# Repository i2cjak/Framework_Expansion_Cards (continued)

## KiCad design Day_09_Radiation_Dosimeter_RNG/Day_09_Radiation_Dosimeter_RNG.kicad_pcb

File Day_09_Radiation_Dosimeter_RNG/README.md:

# Day 09 — Solid-State PIN Radiation Dosimeter & Quantum Decay Hardware RNG

A pocket solid-state ionizing-radiation dosimeter, pulse-height spectrometer, and `/dev/hwrng` true quantum hardware random-number generator built into a `26.0 × 30.0 mm` Framework Laptop Expansion Card.

## Hardware Architecture

1. **Dual Parallel Depleted Silicon PIN Detector (`D3`, `D4` — `2×` OSRAM `BPW34S-Z`, `15.0 mm²` Active Area):**
   - Two `7.5 mm²` intrinsic-layer silicon PIN diodes wired in parallel inside an exposed-ENIG **Faraday & optical shield-can frame** (`10.5 × 10.3 mm` solderable perimeter ring with 12 Faraday stitching vias to the unbroken `In1.Cu` ground plane).
   - Soldering a tinned-steel EMI shield lid (or copper foil tape) over the gold ring blocks visible/IR photons completely while letting X-ray, gamma, and energetic beta particles ionize electron-hole pairs inside the depleted silicon bulk.

2. **`+13.3 V` 4-Stage Dickson Depletion Multiplier & `> 140 dB` Ripple Filter (`D5`, `D6` — `2× BAV99`):**
   - Driven out-of-phase by `TIM1` `100 kHz` push-pull clocks (`PA8` / `PA9`) from `+5.0 V` `VBUS` across three `50 V` flying capacitors (`C11`–`C13`), elevating cathode reverse bias to `+13.3 V` so each `BPW34S-Z` depletes from `72 pF` (`0 V`) down to `~12 pF`.
   - Two cascaded low-pass RC poles (`100 kΩ + 100 nF`, `f_c = 15.9 Hz` followed by `1 MΩ + 100 nF`, `f_c = 1.59 Hz`) attenuate `100 kHz` charge-pump switching ripple below Johnson thermal noise before reaching the PIN cathodes, while an `11:1` divider (`R12`/`R13`) provides closed-loop `HV_RAW` telemetry on `PA0` (`ADC_IN0`).

3. **Femtoamp CMOS Charge-Sensitive Pre-Amplifier & CR-RC Pulse Shaper (`U4`, `U5` — `2×` TI `TLV9061IDBVR`):**
   - Physically separated single-channel `SOT-23-5` CMOS op-amps (`0.5 pA` input bias, `10 MHz` GBW, `10 nV/√Hz` input voltage noise) eliminate dual-op-amp leadframe crosstalk between the high-gain shaper output and the `2.2 pF` charge-integration node.
   - **Stage 1 (`U4` CSA):** `C18 = 2.2 pF C0G` feedback capacitor (`0.45 mV/fC` charge gain) in parallel with `R14 = 10 MΩ` (`τ = 22 µs`) biased at `+0.58 V` (`VBIAS_0V58`) on dedicated RC-isolated analog power (`V33_ANA`).
   - **Stage 2 (`U5` CR-RC Shaper):** `C19 = 100 pF C0G` + `R15 = 2.2 kΩ` differentiator feeding a `-45.5×` active integrator (`R16 = 100 kΩ || C20 = 22 pF C0G`, `τ = 2.2 µs`), converting negative CSA steps into clean positive unipolar pulses (`+0.58 V` baseline to `+3.30 V` full-scale).

4. **Hardware Discriminator, Spectroscopy & Unbiased Quantum Entropy (`U3` — `STM32F072CBT6`):**
   - Crystal-less Full-Speed USB (`HSI48` + `CRS` `1 kHz` USB `SOF` trim) streams conditioned entropy to Linux `/dev/hwrng` and pulse-height histograms over USB CDC.
   - On-chip `DAC1` (`PA4`) sets a software-programmable millivolt threshold on `COMP1_INM`; `PULSE_OUT` on `PA1` triggers `COMP1` (`50 ns`) to timestamp `48 MHz` `TIM2` arrival intervals (`t2 - t1` vs `t4 - t3` unbiased Poisson interval comparison + Von Neumann whitening) and triggers `1 Msps` `ADC_IN1` peak capture for gamma energy spectroscopy.

## Fabrication & Build

All components are sourced from the fab's stock on a `0.8 mm` 4-layer purple-soldermask ENIG stackup (`Day_09_Radiation_Dosimeter_RNG.fab.json`). Regenerate ERC/DRC reports, Gerbers, placement files, STEP model, and 3D renders with:

```bash
python3 build.py
```

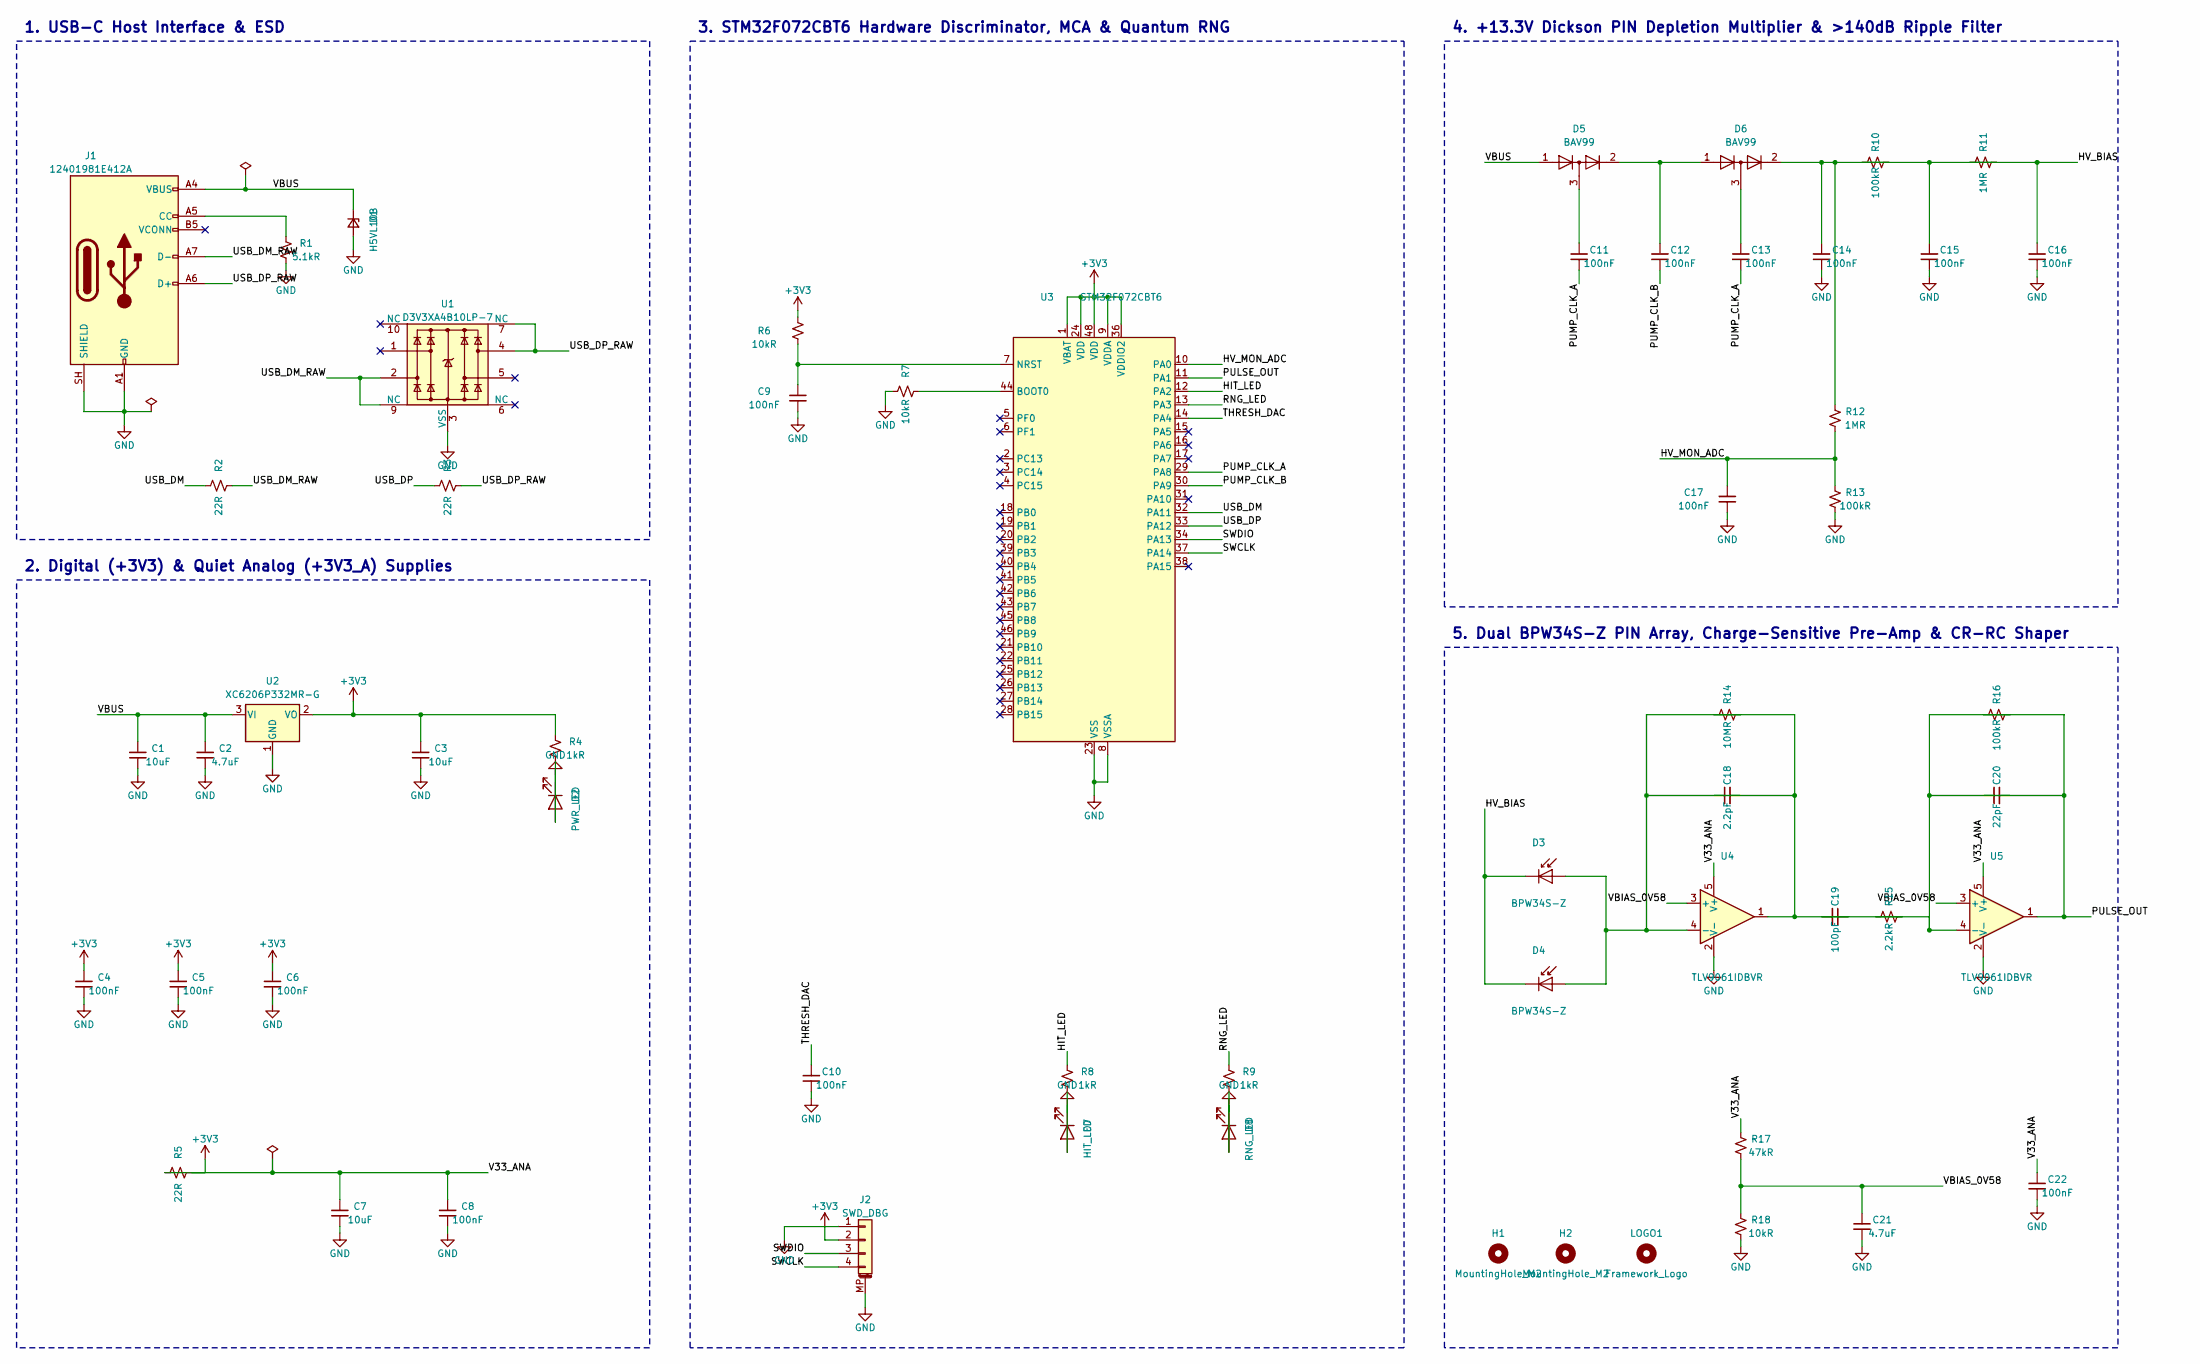
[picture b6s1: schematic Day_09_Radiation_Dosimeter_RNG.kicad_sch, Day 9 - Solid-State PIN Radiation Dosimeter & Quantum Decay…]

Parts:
C1, C3, C7: 10uF; C_0805_2012Metric; MPN CL21A106KAYNNNE; LCSC C15850
C2, C21: 4.7uF; C_0603_1608Metric; MPN CL10A475KO8NNNC; LCSC C19666
C4, C5, C6, C8, C9, C10, C17, C22: 100nF; C_0402_1005Metric; MPN CL05B104KB54PNC; LCSC C307331
C11, C12, C13, C14, C15, C16: 100nF; C_0603_1608Metric; MPN CC0603KRX7R9BB104; LCSC C14663
C18: 2.2pF; C_0603_1608Metric; MPN 0603CG2R2C500NT; LCSC C1651
C19: 100pF; C_0603_1608Metric; MPN CL10C101JB8NNNC; LCSC C14858
C20: 22pF; C_0603_1608Metric; MPN CL10C220JB8NNNC; LCSC C1653
D1: H5VL10B; D_SOD-882; MPN H5VL10B; LCSC C7420372
D2: PWR_LED; LED_0603_1608Metric; MPN KT-0603G; LCSC C2297
D3, D4: BPW34S-Z; Osram_BPW34S-SMD; MPN BPW34S-Z; LCSC C67891
D5, D6: BAV99; SOT-23; MPN BAV99; LCSC C7420336
D7: HIT_LED; LED_0603_1608Metric; MPN KT-0603R; LCSC C2286
D8: RNG_LED; LED_0603_1608Metric; MPN KT-0603W; LCSC C2290
H1, H2: MountingHole_M2; MountingHole_2.2mm_M2
J1: 12401981E412A; USB_C_Plug_Amphenol_12401981E412A; MPN 12401981E412A; LCSC C5428559
J2: SWD_DBG; JST_SH_SM04B-SRSS-TB_1x04-1MP_P1.00mm_Horizontal; MPN SM04B-SRSS-TB(LF)(SN); LCSC C160404
LOGO1: Framework_Logo; Framework-Logo_1.5mm_SilkScreen
R1: 5.1kR; R_0402_1005Metric; MPN 0402WGF5101TCE; LCSC C25905
R2, R3, R5: 22R; R_0402_1005Metric; MPN 0402WGF220JTCE; LCSC C25092
R4, R8, R9: 1kR; R_0402_1005Metric; MPN 0402WGF1001TCE; LCSC C11702
R6, R7, R18: 10kR; R_0402_1005Metric; MPN 0402WGF1002TCE; LCSC C25744
R10, R13, R16: 100kR; R_0402_1005Metric; MPN 0402WGF1003TCE; LCSC C25741
R11, R12: 1MR; R_0603_1608Metric; MPN 0603WAF1004T5E; LCSC C22935
R14: 10MR; R_0603_1608Metric; MPN 0603WAF1005T5E; LCSC C7250
R15: 2.2kR; R_0402_1005Metric; MPN 0402WGF2201TCE; LCSC C25879
R17: 47kR; R_0402_1005Metric; MPN 0402WGF4702TCE; LCSC C25792
U1: D3V3XA4B10LP-7; Diodes_UDFN-10_1x2.5mm_P0.5mm; MPN D3V3XA4B10LP-7; LCSC C1980462
U2: XC6206P332MR-G; SOT-23; MPN XC6206P332MR-G; LCSC C5446
U3: STM32F072CBT6; LQFP-48_7x7mm_P0.5mm; MPN STM32F072CBT6; LCSC C81720
U4, U5: TLV9061IDBVR; SOT-23-5; MPN TLV9061IDBVR; LCSC C398358

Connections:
/HIT_LED: R8.1, U3.12 (PA2)
/HV_BIAS: C16.1, D3.1 (K), D4.1 (K), R11.1
/HV_MON_ADC: C17.1, R12.2, R13.1, U3.10 (PA0)
/PULSE_OUT: C20.1, R16.1, U3.11 (PA1), U5.1
/PUMP_CLK_A: C11.2, C13.2, U3.29 (PA8)
/PUMP_CLK_B: C12.2, U3.30 (PA9)
/RNG_LED: R9.1, U3.13 (PA3)
/SWCLK: J2.4, U3.37 (PA14)
/SWDIO: J2.3, U3.34 (PA13)
/THRESH_DAC: C10.1, U3.14 (PA4)
/USB_DM: R2.1, U3.32 (PA11)
/USB_DM_RAW: J1.A7 (D-), R2.2, U1.2, U1.9 (NC)
/USB_DP: R3.1, U3.33 (PA12)
/USB_DP_RAW: J1.A6 (D+), R3.2, U1.4, U1.7 (NC)
/V33_ANA: C7.1, C8.1, C22.1, R5.1, R17.1, U4.5 (V+), U5.5 (V+)
/VBIAS_0V58: C21.1, R17.2, R18.1, U4.3 (+), U5.3 (+)
/VBUS: C1.1, C2.1, D1.1 (K), D5.1 (K), J1.A4 (VBUS), J1.A9 (VBUS), J1.B4 (VBUS), J1.B9 (VBUS), U2.3 (VI)
unnamed: C11.1, D5.3 (K)
unnamed: C13.1, D6.3 (K)
unnamed: C15.1, R10.1, R11.2
unnamed: C18.1, C19.2, R14.1, U4.1
unnamed: C19.1, R15.2
unnamed: C18.2, D3.2 (A), D4.2 (A), R14.2, U4.4 (-)
unnamed: C12.1, D5.2 (A), D6.1 (K)
unnamed: C14.1, D6.2 (A), R10.2, R12.1
unnamed: J1.A5 (CC), R1.1
unnamed: R7.2, U3.44 (BOOT0)
unnamed: C9.1, R6.2, U3.7 (NRST)
unnamed: C20.2, R15.1, R16.2, U5.4 (-)

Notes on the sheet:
1. USB-C Host Interface & ESD
2. Digital (+3V3) & Quiet Analog (+3V3_A) Supplies
3. STM32F072CBT6 Hardware Discriminator, MCA & Quantum RNG
4. +13.3V Dickson PIN Depletion Multiplier & >140dB Ripple Filter
5. Dual BPW34S-Z PIN Array, Charge-Sensitive Pre-Amp & CR-RC Shaper

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
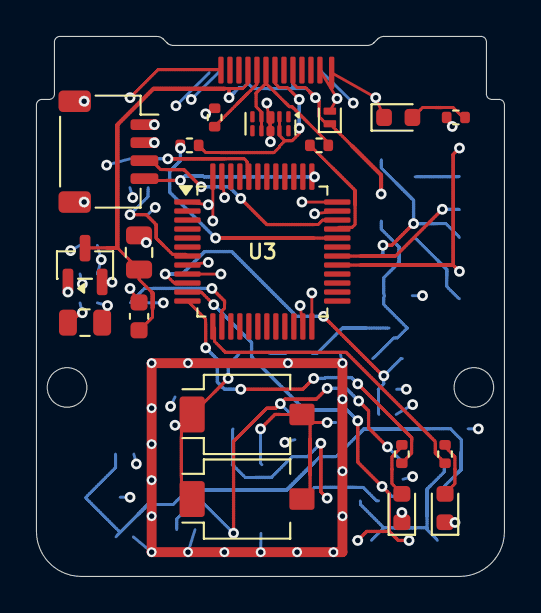
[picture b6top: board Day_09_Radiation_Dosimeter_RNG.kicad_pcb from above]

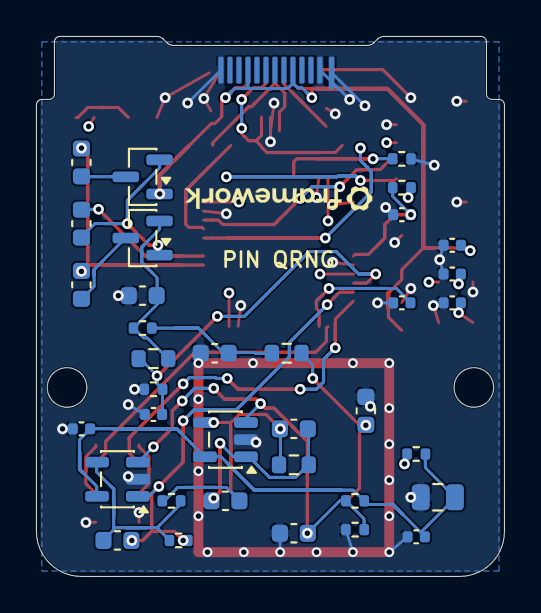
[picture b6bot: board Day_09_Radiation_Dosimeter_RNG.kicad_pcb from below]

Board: 4 copper layers, 26.0 x 30.0 mm, 58 parts (36 on the bottom side), 34 nets.

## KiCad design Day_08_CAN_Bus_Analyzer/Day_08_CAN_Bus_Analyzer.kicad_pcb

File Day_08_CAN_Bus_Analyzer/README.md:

# Day 08 — `1 Mbps` ISO-11898 CAN 2.0B Bus Analyzer (`gs_usb` SocketCAN)

A flush-fitting Framework Laptop Expansion Card implementing a native Linux mainline **`gs_usb` / candleLight SocketCAN** `1 Mbps` ISO-11898-2 CAN 2.0B analyzer with **galvanically isolated solid-state `120 Ω` termination switching**, hardware listen-only mode, `±24 V` automotive surge clamping, and `0–36.3 V` CAN-harness supply rail telemetry on a locking DroneCAN/Cyphal `4`-pin JST-GH bezel port.

---

## Hardware Architecture & Engineering Decisions

### 1. Simultaneous Full-Speed USB + `1 Mbps` `bxCAN` (`STM32F072CBT6` + `±10 ppm` Quartz)
- Unlike `STM32F103x8` devices (which share a single 512 B SRAM block and IRQ vector between USB and `CAN1`), **`U3` (`STM32F072CBT6`)** provides a dedicated `1 KB` USB packet buffer at `0x40006000` (`PA11`/`PA12`) alongside an independent `bxCAN` controller (`PB8`/`PB9`), sustaining **100% `1 Mbps` CAN bus load** over USB without dropped frames.
- **`Y1` (`X32258MOB4SI` `8.000 MHz` `±10 ppm` `3225` quartz crystal)** clocks the `bxCAN` bit-timing engine (`48.000 MHz` via `×6` PLL: `BRP = 3`, `16 TQ`, `TS1 = 13`, `TS2 = 2`, `87.5%` CiA sample point), exceeding ISO-11898-1 oscillator accuracy (`±0.15%`) by **`150×`** while `HSI48` + `CRS` clocks USB Full-Speed.

### 2. Opto-Isolated `120 Ω` PhotoMOS Solid-State Termination (`TLP172AM`)
- Switching a `120 Ω` resistor across a differential CAN bus with a bare GPIO-driven N-MOSFET fails under common-mode excursions (`-2 V` to `+7 V` operational, `±24 V` fault) due to `V_GS` modulation and body-diode conduction.
- **`U5` (Toshiba `TLP172AM` `SOP-4` PhotoMOS solid-state relay, `60 V` blocking, `1.0 Ω` `R_on`, `3.75 kVrms` isolation)** places back-to-back optically driven MOSFETs in series with **`R14` (`120 Ω` `1%` `0805` `125 mW`)**:
  - **Enabled (`PB1 = HIGH`):** `R_term = 120.0 + 1.0 = 121.0 Ω` (within `< 1%` of nominal `120 Ω`, ISO-11898 window `118–130 Ω`), illuminating the bezel `TERM` indicator (`D5`).
  - **Disabled (`PB1 = LOW`):** Bidirectional `±60 V` open circuit with `< 15 pF` symmetric off-capacitance and zero ground-loop or common-mode coupling—toggleable directly via `ip link set can0 type can termination 120`.

### 3. Transceiver, `±24 V` Automotive Protection & `0–36 V` DroneCAN Bus Sense
- **`U4` (`SN65HVD230DR`):** `3.3 V` `1 Mbps` ISO-11898 transceiver with `R9` (`10 kΩ` recessive pull-up on `D` during MCU reset) and `PB0`-controlled `Rs` pin supporting hardware **Listen-Only / Silent** mode (`ip link set can0 type can listen-only on`).
- **`D6` (`PESD2CAN` `SOT-23`) + `C13`/`C14` (`22 pF` `50 V` `C0G`):** Dual bidirectional `24 V` CAN surge clamp (`IEC 61000-4-2 ±30 kV`) placed immediately behind **`J2` (`SM04B-GHS-TB` locking 4-pin `1.25 mm` JST-GH)** wired to the standard **DroneCAN / Cyphal / Pixhawk / VESC** pinout (`1: V_CAN`, `2: CAN_H`, `3: CAN_L`, `4: GND`).
- **`V_CAN` Voltage Sense (`PA0 / ADC_IN0`):** `100 kΩ / 10 kΩ` `1%` divider (`11:1`, `0–36.3 V` full-scale) filtered by `100 nF` (`C15`) and clamped by `D7` (`H5VL10B` TVS), strictly isolated from host `VBUS` so external `12 V / 24 V` vehicle or drone batteries can never back-feed the laptop.

---

## Building PCB & Firmware

```bash
# Regenerate ERC/DRC reports, Gerbers, BOM/CPL (from the fab's stock), and 3D renders
cd Day_08_CAN_Bus_Analyzer && python3 build.py

# Compile STM32F072CBT6 gs_usb / bxCAN firmware
make -C firmware
```

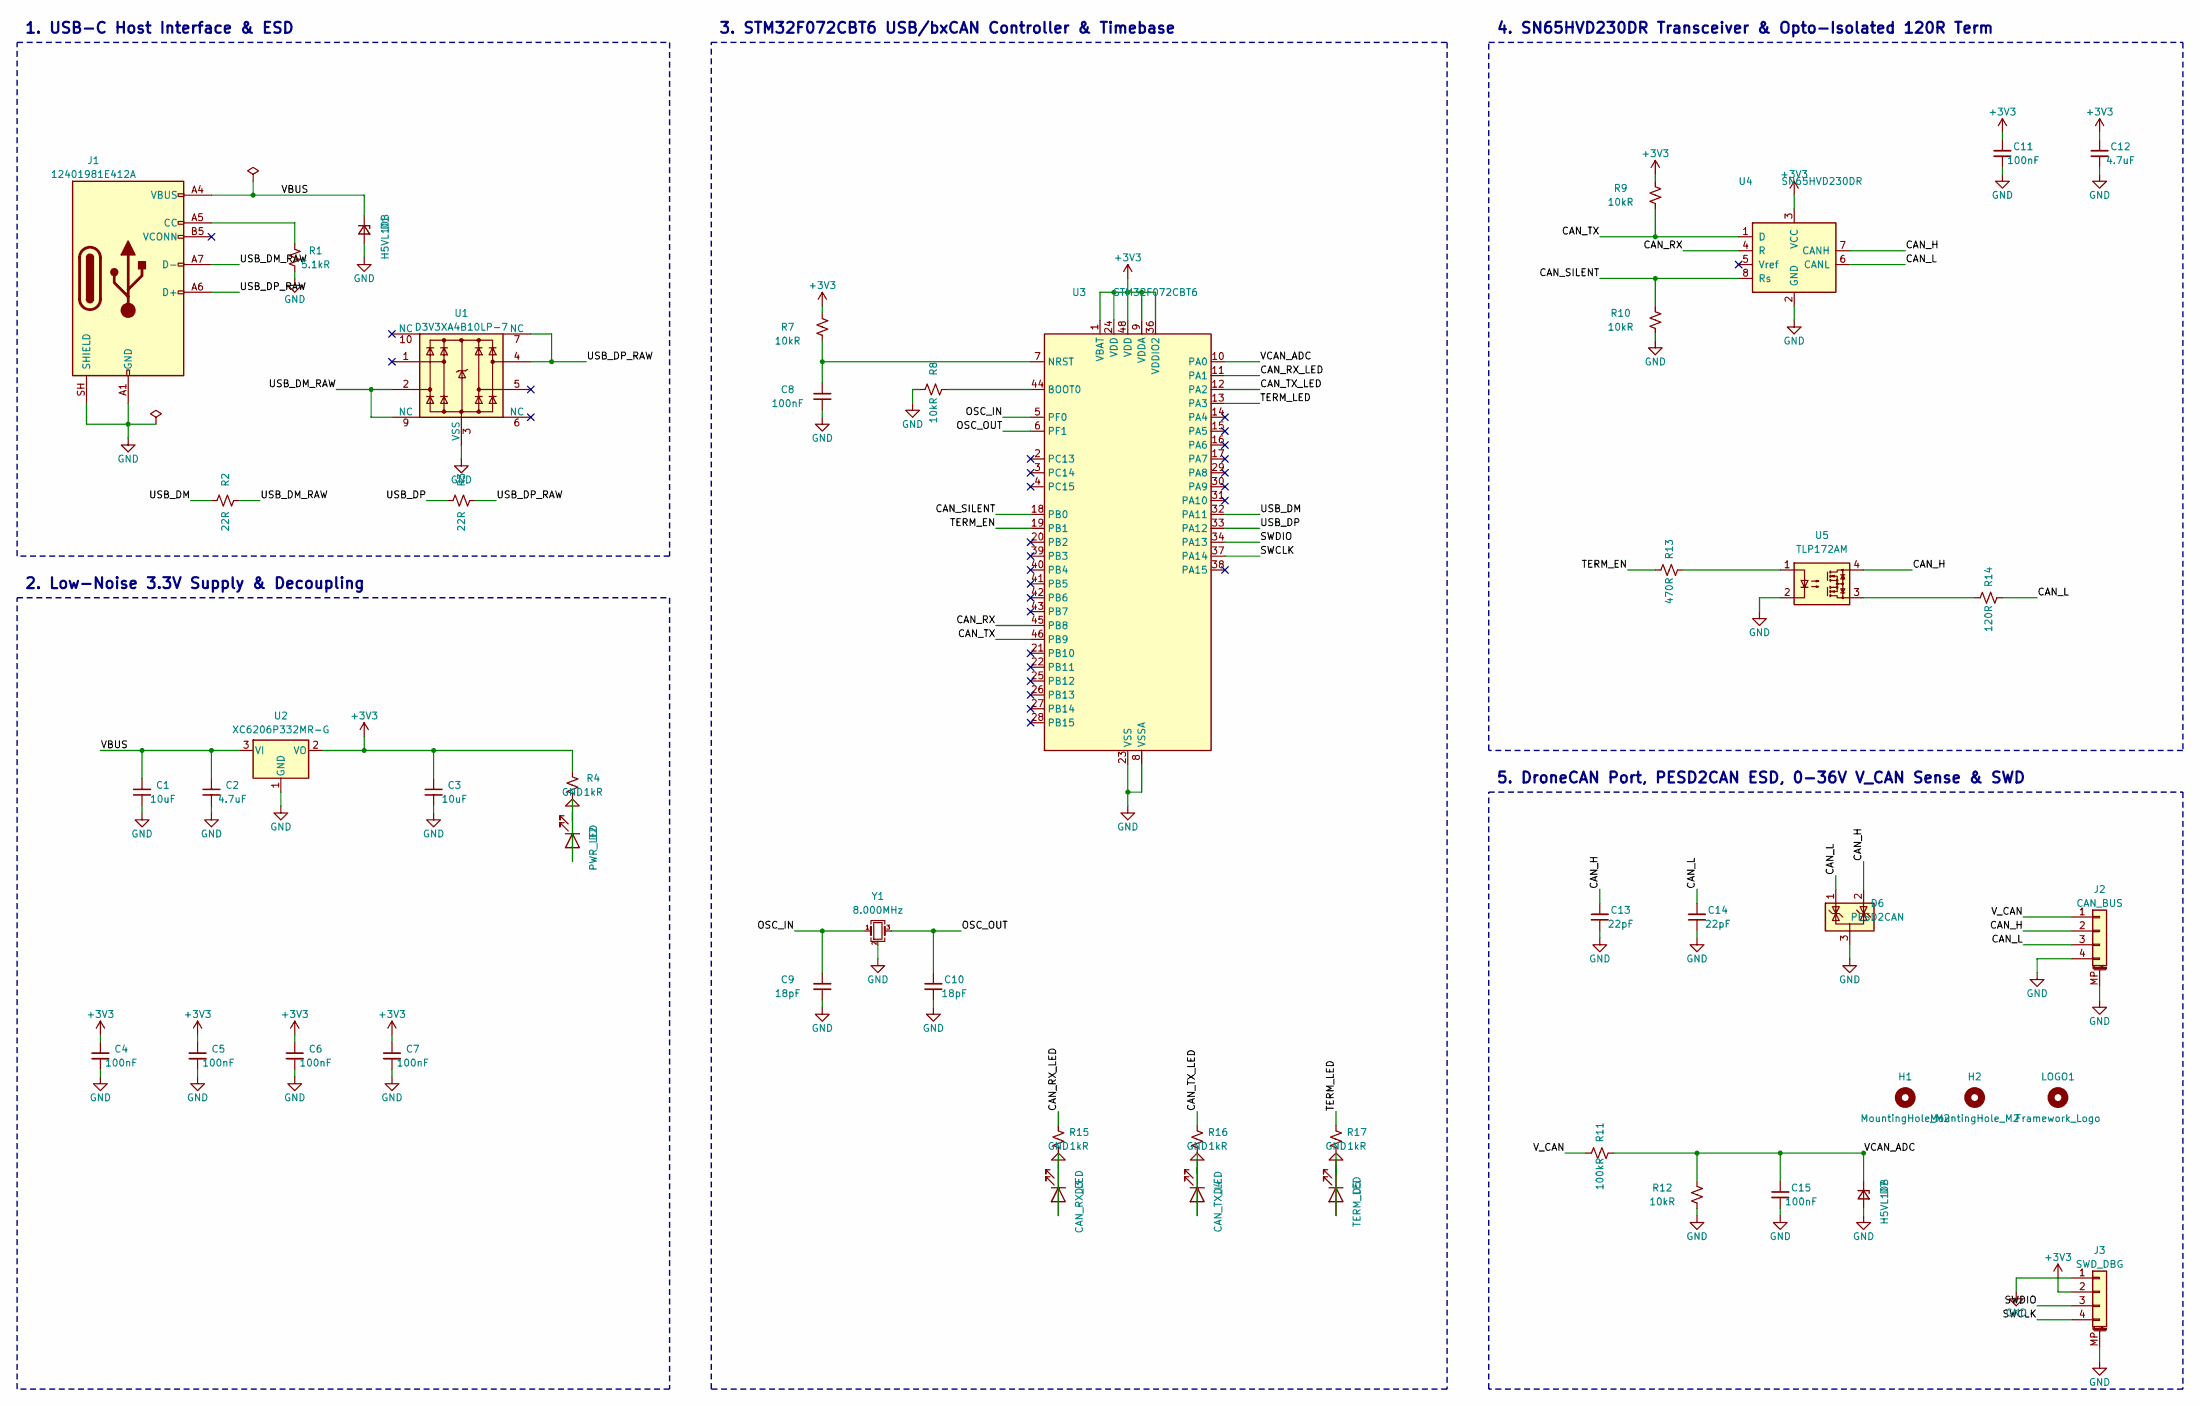
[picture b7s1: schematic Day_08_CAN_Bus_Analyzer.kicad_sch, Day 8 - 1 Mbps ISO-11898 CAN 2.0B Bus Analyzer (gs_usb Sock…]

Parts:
C1, C3: 10uF; C_0805_2012Metric; MPN CL21A106KAYNNNE; LCSC C15850
C2, C12: 4.7uF; C_0603_1608Metric; MPN CL10A475KO8NNNC; LCSC C19666
C4, C5, C6, C7, C8, C11, C15: 100nF; C_0402_1005Metric; MPN CL05B104KB54PNC; LCSC C307331
C9, C10: 18pF; C_0402_1005Metric; MPN 0402CG180J500NT; LCSC C1549
C13, C14: 22pF; C_0402_1005Metric; MPN 0402CG220J500NT; LCSC C1555
D1, D7: H5VL10B; D_SOD-882; MPN H5VL10B; LCSC C7420372
D2: PWR_LED; LED_0603_1608Metric; MPN KT-0603W; LCSC C2290
D3: CAN_RX_LED; LED_0603_1608Metric; MPN KT-0603W; LCSC C2290
D4: CAN_TX_LED; LED_0603_1608Metric; MPN KT-0603R; LCSC C2286
D5: TERM_LED; LED_0603_1608Metric; MPN KT-0603R; LCSC C2286
D6: PESD2CAN; SOT-23; MPN PESD2CAN; LCSC C2687131
H1, H2: MountingHole_M2; MountingHole_2.2mm_M2
J1: 12401981E412A; USB_C_Plug_Amphenol_12401981E412A; MPN 12401981E412A; LCSC C5428559
J2: CAN_BUS; JST_GH_SM04B-GHS-TB_1x04-1MP_P1.25mm_Horizontal; MPN SM04B-GHS-TB(LF)(SN); LCSC C189895
J3: SWD_DBG; JST_SH_SM04B-SRSS-TB_1x04-1MP_P1.00mm_Horizontal; MPN SM04B-SRSS-TB(LF)(SN); LCSC C160404
LOGO1: Framework_Logo; Framework-Logo_1.5mm_SilkScreen
R1: 5.1kR; R_0402_1005Metric; MPN 0402WGF5101TCE; LCSC C25905
R2, R3: 22R; R_0402_1005Metric; MPN 0402WGF220JTCE; LCSC C25092
R4, R15, R16, R17: 1kR; R_0402_1005Metric; MPN 0402WGF1001TCE; LCSC C11702
R7, R8, R9, R10, R12: 10kR; R_0402_1005Metric; MPN 0402WGF1002TCE; LCSC C25744
R11: 100kR; R_0402_1005Metric; MPN 0402WGF1003TCE; LCSC C25741
R13: 470R; R_0402_1005Metric; MPN 0402WGF4700TCE; LCSC C25117
R14: 120R; R_0805_2012Metric; MPN 0805W8F1200T5E; LCSC C17437
U1: D3V3XA4B10LP-7; Diodes_UDFN-10_1x2.5mm_P0.5mm; MPN D3V3XA4B10LP-7; LCSC C1980462
U2: XC6206P332MR-G; SOT-23; MPN XC6206P332MR-G; LCSC C5446
U3: STM32F072CBT6; LQFP-48_7x7mm_P0.5mm; MPN STM32F072CBT6; LCSC C81720
U4: SN65HVD230DR; SOIC-8_3.9x4.9mm_P1.27mm; MPN SN65HVD230DR; LCSC C12084
U5: TLP172AM; SOP-4_3.8x4.1mm_P2.54mm; MPN TLP172AM(TPL,E; LCSC C2152276
Y1: 8.000MHz; Crystal_SMD_3225-4Pin_3.2x2.5mm; MPN X32258MOB4SI; LCSC C2682775

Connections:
/CAN_H: C13.1, D6.2 (K), J2.2, U4.7 (CANH), U5.4
/CAN_L: C14.1, D6.1 (K), J2.3, R14.2, U4.6 (CANL)
/CAN_RX: U3.45 (PB8), U4.4 (R)
/CAN_RX_LED: R15.1, U3.11 (PA1)
/CAN_SILENT: R10.1, U3.18 (PB0), U4.8 (Rs)
/CAN_TX: R9.2, U3.46 (PB9), U4.1 (D)
/CAN_TX_LED: R16.1, U3.12 (PA2)
/OSC_IN: C9.1, U3.5 (PF0), Y1.1
/OSC_OUT: C10.1, U3.6 (PF1), Y1.3
/SWCLK: J3.4, U3.37 (PA14)
/SWDIO: J3.3, U3.34 (PA13)
/TERM_EN: R13.1, U3.19 (PB1)
/TERM_LED: R17.1, U3.13 (PA3)
/USB_DM: R2.1, U3.32 (PA11)
/USB_DM_RAW: J1.A7 (D-), R2.2, U1.2, U1.9 (NC)
/USB_DP: R3.1, U3.33 (PA12)
/USB_DP_RAW: J1.A6 (D+), R3.2, U1.4, U1.7 (NC)
/VBUS: C1.1, C2.1, D1.1 (K), J1.A4 (VBUS), J1.A9 (VBUS), J1.B4 (VBUS), J1.B9 (VBUS), U2.3 (VI)
/VCAN_ADC: C15.1, D7.1 (K), R11.2, R12.1, U3.10 (PA0)
/V_CAN: J2.1, R11.1
unnamed: J1.A5 (CC), R1.1
unnamed: R13.2, U5.1
unnamed: R14.1, U5.3
unnamed: R8.2, U3.44 (BOOT0)
unnamed: C8.1, R7.2, U3.7 (NRST)

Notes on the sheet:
1. USB-C Host Interface & ESD
2. Low-Noise 3.3V Supply & Decoupling
3. STM32F072CBT6 USB/bxCAN Controller & Timebase
4. SN65HVD230DR Transceiver & Opto-Isolated 120R Term
5. DroneCAN Port, PESD2CAN ESD, 0-36V V_CAN Sense & SWD

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
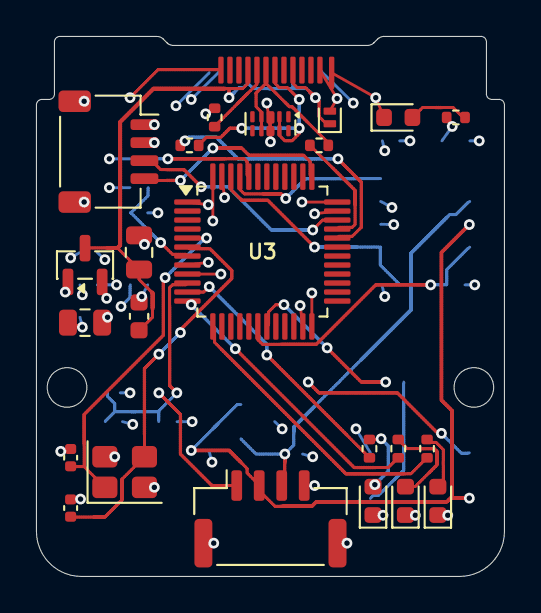
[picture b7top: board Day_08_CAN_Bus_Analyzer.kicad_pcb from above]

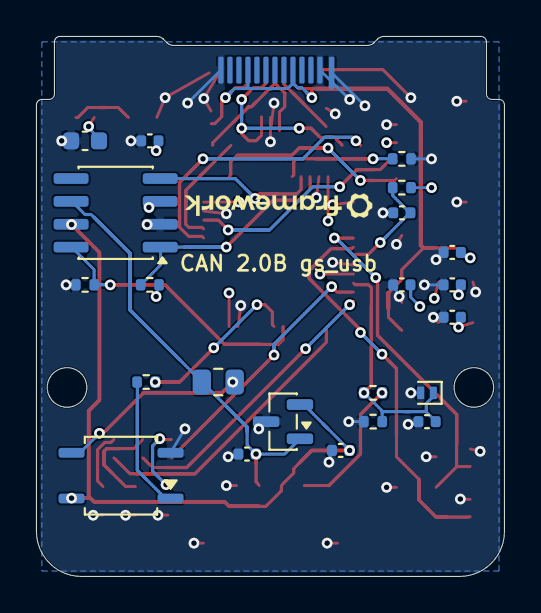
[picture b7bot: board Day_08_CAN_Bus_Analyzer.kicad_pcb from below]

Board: 4 copper layers, 26.0 x 30.0 mm, 49 parts (23 on the bottom side), 31 nets.

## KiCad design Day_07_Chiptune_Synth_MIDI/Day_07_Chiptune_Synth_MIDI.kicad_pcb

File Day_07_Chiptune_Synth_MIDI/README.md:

# Day 07 — Polyphonic FM / Chiptune Hardware Synthesizer & Type-A MIDI Expansion Card

A pocket hardware music workstation inside a `26.0 × 30.0 mm` Framework Expansion Card bay (`IDEAS.md` Concept #10). Enumerates over USB-C as a class-compliant **USB-MIDI 1.0** instrument using crystal-less `HSI48` USB-SOF clock recovery (`CRS`), synthesizes **4-voice polyphonic 2-operator FM + pulse/duty + wavetable/triangle + LFSR noise chiptune audio** in real time on an `STM32F072CBT6`, streams `48 kHz` stereo digital audio over hardware `I2S2` into a **Texas Instruments `PCM5102APWR` 32-bit / 384 kHz DirectPath™ charge-pump DAC** (`112 dB` SNR, ground-centered `2.1 Vrms` stereo output with zero DC-blocking output capacitors), and provides both a **gold-plated `3.5 mm` stereo headphone/line-out jack (`J2`)** and a **locking `1.25 mm` 3-pin MMA Type-A hardware MIDI Out port (`J3`)** plus a **4-channel front-bezel voice activity LED bar (`D3..D6`)**.

---

## Architecture & Key Specifications

| Subsystem | Implementation | Key Rating / Performance |
| :--- | :--- | :--- |
| **USB-MIDI & Synth Engine (`U3`)** | `STM32F072CBT6` (`48 MHz` Cortex-M0, `128 KB` Flash, `16 KB` SRAM) | Crystal-less `HSI48` trimmed to `±0.05%` via `1 kHz` USB `SOF` (`CRS`); hardware `I2S2` master + `USART1` `31.25 kbaud` MIDI |
| **Stereo Audio DAC (`U4`)** | `PCM5102APWR` (`TSSOP-20`, internal negative charge pump + internal PLL) | `32-bit / 384 kHz` max (`48 kHz` native synth engine), `112 dB` dynamic range, `-93 dB` THD+N, `2.1 Vrms` ground-centered DirectPath™ output (`SCK=GND` 3-wire BCK-PLL mode) |
| **Stereo Output (`J2`)** | `PJ-320D-4A` gold-plated `3.5 mm` SMD TRS/TRRS jack + `22 Ω` series isolation (`R5`, `R6`) | Drives studio line inputs and `32 Ω+` headphones directly down to `0 Hz` without bass roll-off |
| **Hardware MIDI Out (`J3`)** | Locking `1.25 mm` 3-pin JST-GH (`SM03B-GHS-TB`) wired per **MMA 3.3 V Type-A TRS MIDI** | Pin 1 (`Tip/Sink`) via `22 Ω` (`R9`) from `PA9/USART1_TX`, Pin 2 (`Ring/Source`) via `22 Ω` (`R10`) from `+3V3`, Pin 3 (`Sleeve`) = `GND` |
| **Front-Bezel Voice Bar (`D3..D6`)** | 4× `0603` SMD LEDs (`PA0..PA3`, alternating Red/White) | Per-voice gate & envelope trigger indicators (Voices 1–2 FM/Pulse, Voice 3 Triangle/Wave, Voice 4 LFSR Noise/Drums) |
| **USB Protection & Power** | `H5VL10B` TVS (`D1`), `D3V3XA4B10LP-7` low-cap ESD (`U1`), `XC6206P332MR-G` `3.3 V` LDO (`U2`) | `5.1 kΩ` `CC1` sink (`R1`), `< 45 mA` total card draw from `5 V` `VBUS` |
| **4-Layer Stackup** | `0.8 mm` 4-Layer Red ENIG (`F.Cu` / `In1.Cu GND` / `In2.Cu +3V3` / `B.Cu GND`) | Unbroken `In1.Cu` ground reference plane isolating digital USB/MCU return currents from analog `OUTL`/`OUTR` |

---

## Pin Map (`STM32F072CBT6`)

| MCU Pin | Signal | Target / Function |
| :--- | :--- | :--- |
| `PA11` / `PA12` | `USB_DM` / `USB_DP` | USB 2.0 Full-Speed Device (`USB-MIDI 1.0` + `CRS` `1 kHz` SOF trim, via `22 Ω` `R2`/`R3` + `U1` ESD) |
| `PB12` (`I2S2_WS`) | `I2S_LRCK` | `PCM5102A` Pin 15 (`LRCK`, `48 kHz` stereo frame clock) |
| `PB13` (`I2S2_CK`) | `I2S_BCK` | `PCM5102A` Pin 13 (`BCK`, `1.536 MHz` bit clock; drives `PCM5102A` internal PLL with `SCK=GND`) |
| `PB15` (`I2S2_SD`) | `I2S_DIN` | `PCM5102A` Pin 14 (`DIN`, 16-bit/32-bit stereo I2S PCM stream) |
| `PB14` | `DAC_XSMT` | `PCM5102A` Pin 17 (`XSMT` soft-mute control; `10 kΩ` pull-down `R15` keeps DAC pop-free during reset) |
| `PA9` (`USART1_TX`) | `MIDI_TX` | `31,250 baud` 8N1 Hardware MIDI Out (`R9 = 22 Ω` sink, `R10 = 22 Ω` `+3V3` source on `J3`) |
| `PA0 .. PA3` | `VOICE_LED1..4` | Front-bezel 4-channel polyphonic voice gate LEDs (`D3..D6`) |
| `PA13` / `PA14` | `SWDIO` / `SWCLK` | `J4` 4-pin `1.0 mm` JST-SH SWD debug & flash header |

---

## Building & Verifying

### Hardware (KiCad 10 ERC, DRC, Gerbers, BOM, 3D STEP & Renders)
```bash
cd Day_07_Chiptune_Synth_MIDI
python3 build.py
```
- **ERC:** `0` errors, `0` warnings
- **DRC:** `0` violations, `0` unconnected items, `0` schematic parity issues
- **Fabrication Spec:** [`Day_07_Chiptune_Synth_MIDI.fab.json`](./Day_07_Chiptune_Synth_MIDI.fab.json) (`4` layers, `0.8 mm` thickness, Red solder mask, ENIG finish, all SMD components verified in stock at the fab)

### Firmware (`arm-none-eabi-gcc`)
```bash
cd Day_07_Chiptune_Synth_MIDI/firmware
make
```
Builds `build/chiptune_synth_midi.elf` and `.bin` with `0` warnings — configuring `HSI48` + `CRS` USB-SOF auto-trimming, `SPI2`/`I2S2` `48 kHz` master audio streaming to `PCM5102APWR` (`PB14` pop-free unmute sequencing), `31,250 baud` `USART1` hardware MIDI Out mirroring, 4-voice DDS phase-accumulated FM / pulse / triangle / 15-bit LFSR percussion synthesis, and `PA0..PA3` voice activity LEDs.

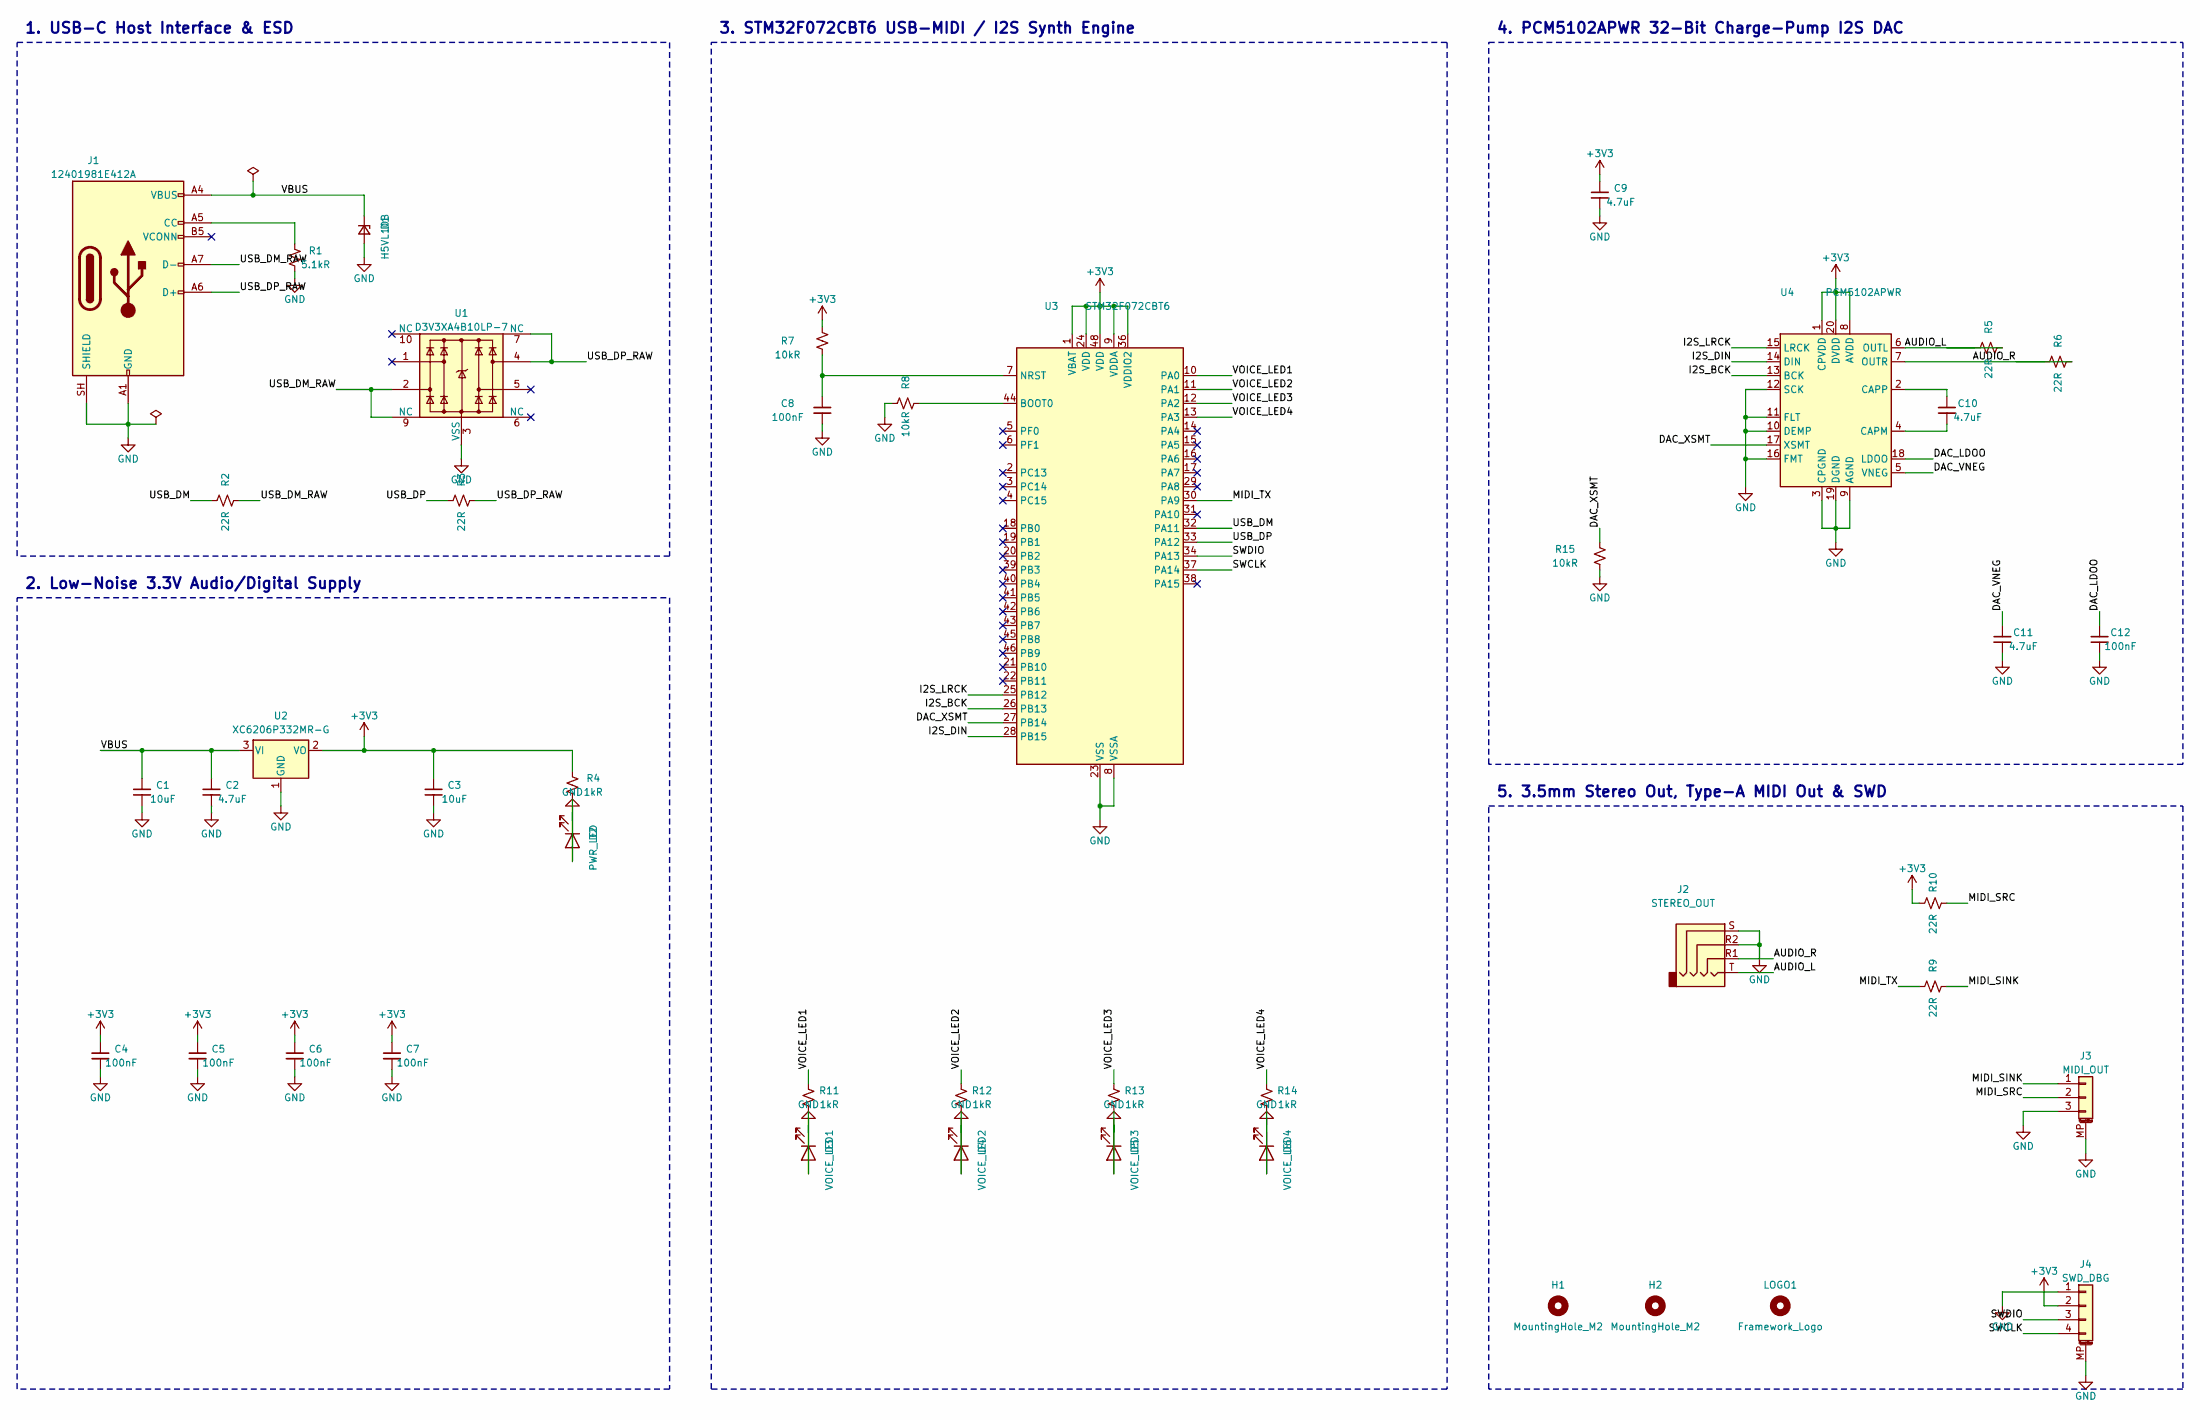
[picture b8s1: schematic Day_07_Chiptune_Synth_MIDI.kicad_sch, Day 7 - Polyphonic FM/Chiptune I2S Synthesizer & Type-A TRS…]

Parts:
C1, C3: 10uF; C_0805_2012Metric; MPN CL21A106KAYNNNE; LCSC C15850
C2, C9, C10, C11: 4.7uF; C_0603_1608Metric; MPN CL10A475KO8NNNC; LCSC C19666
C4, C5, C6, C7, C8, C12: 100nF; C_0402_1005Metric; MPN CL05B104KB54PNC; LCSC C307331
D1: H5VL10B; D_SOD-882; MPN H5VL10B; LCSC C7420372
D2: PWR_LED; LED_0603_1608Metric; MPN KT-0603W; LCSC C2290
D3: VOICE_LED1; LED_0603_1608Metric; MPN KT-0603R; LCSC C2286
D4: VOICE_LED2; LED_0603_1608Metric; MPN KT-0603W; LCSC C2290
D5: VOICE_LED3; LED_0603_1608Metric; MPN KT-0603R; LCSC C2286
D6: VOICE_LED4; LED_0603_1608Metric; MPN KT-0603W; LCSC C2290
H1, H2: MountingHole_M2; MountingHole_2.2mm_M2
J1: 12401981E412A; USB_C_Plug_Amphenol_12401981E412A; MPN 12401981E412A; LCSC C5428559
J2: STEREO_OUT; PJ-320D-4A_Bezel; MPN PJ-320D-4A; LCSC C95562
J3: MIDI_OUT; JST_GH_SM03B-GHS-TB_1x03-1MP_P1.25mm_Horizontal; MPN SM03B-GHS-TB(LF)(SN); LCSC C514175
J4: SWD_DBG; JST_SH_SM04B-SRSS-TB_1x04-1MP_P1.00mm_Horizontal; MPN SM04B-SRSS-TB(LF)(SN); LCSC C160404
LOGO1: Framework_Logo; Framework-Logo_1.5mm_SilkScreen
R1: 5.1kR; R_0402_1005Metric; MPN 0402WGF5101TCE; LCSC C25905
R2, R3, R5, R6, R9, R10: 22R; R_0402_1005Metric; MPN 0402WGF220JTCE; LCSC C25092
R4, R11, R12, R13, R14: 1kR; R_0402_1005Metric; MPN 0402WGF1001TCE; LCSC C11702
R7, R8, R15: 10kR; R_0402_1005Metric; MPN 0402WGF1002TCE; LCSC C25744
U1: D3V3XA4B10LP-7; Diodes_UDFN-10_1x2.5mm_P0.5mm; MPN D3V3XA4B10LP-7; LCSC C1980462
U2: XC6206P332MR-G; SOT-23; MPN XC6206P332MR-G; LCSC C5446
U3: STM32F072CBT6; LQFP-48_7x7mm_P0.5mm; MPN STM32F072CBT6; LCSC C81720
U4: PCM5102APWR; TSSOP-20_4.4x6.5mm_P0.65mm; MPN PCM5102APWR; LCSC C107671

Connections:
/AUDIO_L: J2.T, R5.1, R5.2, U4.6 (OUTL)
/DAC_LDOO: C12.1, U4.18 (LDOO)
/DAC_VNEG: C11.1, U4.5 (VNEG)
/DAC_XSMT: R15.1, U3.27 (PB14), U4.17 (XSMT)
/I2S_BCK: U3.26 (PB13), U4.13 (BCK)
/I2S_DIN: U3.28 (PB15), U4.14 (DIN)
/I2S_LRCK: U3.25 (PB12), U4.15 (LRCK)
/MIDI_SINK: J3.1, R9.2
/MIDI_SRC: J3.2, R10.2
/MIDI_TX: R9.1, U3.30 (PA9)
/SWCLK: J4.4, U3.37 (PA14)
/SWDIO: J4.3, U3.34 (PA13)
/USB_DM: R2.1, U3.32 (PA11)
/USB_DM_RAW: J1.A7 (D-), R2.2, U1.2, U1.9 (NC)
/USB_DP: R3.1, U3.33 (PA12)
/USB_DP_RAW: J1.A6 (D+), R3.2, U1.4, U1.7 (NC)
/VBUS: C1.1, C2.1, D1.1 (K), J1.A4 (VBUS), J1.A9 (VBUS), J1.B4 (VBUS), J1.B9 (VBUS), U2.3 (VI)
/VOICE_LED1: R11.1, U3.10 (PA0)
/VOICE_LED2: R12.1, U3.11 (PA1)
/VOICE_LED3: R13.1, U3.12 (PA2)
/VOICE_LED4: R14.1, U3.13 (PA3)
unnamed: J1.A5 (CC), R1.1
unnamed: R8.2, U3.44 (BOOT0)
unnamed: C8.1, R7.2, U3.7 (NRST)
unnamed: C10.2, U4.4 (CAPM)
unnamed: C10.1, U4.2 (CAPP)

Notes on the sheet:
1. USB-C Host Interface & ESD
2. Low-Noise 3.3V Audio/Digital Supply
3. STM32F072CBT6 USB-MIDI / I2S Synth Engine
4. PCM5102APWR 32-Bit Charge-Pump I2S DAC
5. 3.5mm Stereo Out, Type-A MIDI Out & SWD

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
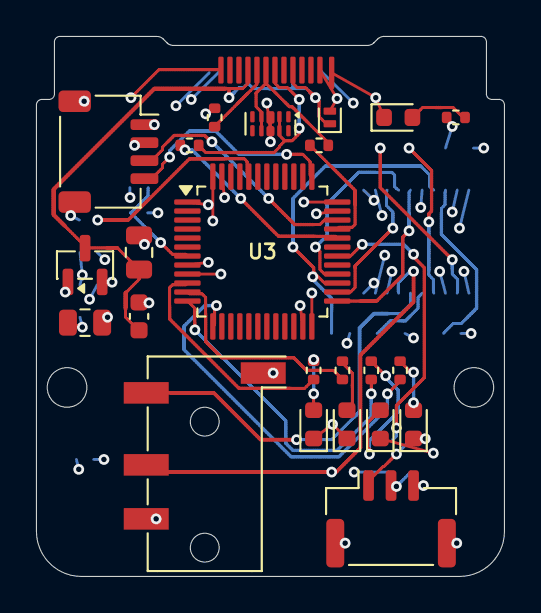
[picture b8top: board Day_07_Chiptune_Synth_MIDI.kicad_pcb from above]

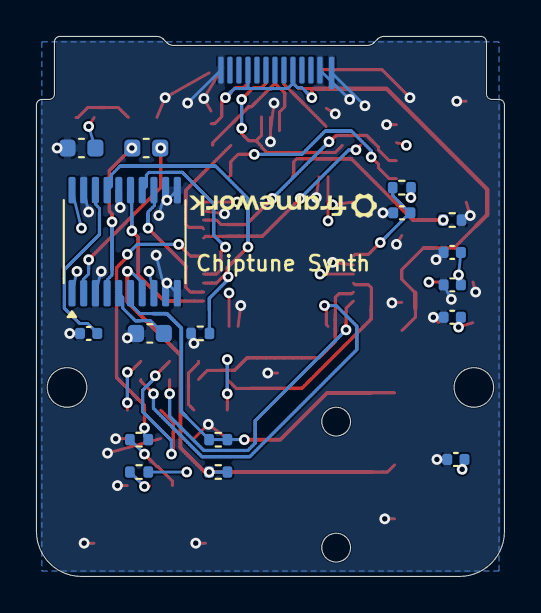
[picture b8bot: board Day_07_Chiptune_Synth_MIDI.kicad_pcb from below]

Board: 4 copper layers, 26.0 x 30.0 mm, 44 parts (18 on the bottom side), 34 nets.

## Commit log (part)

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2026-04-28 Initial commit.
2026-04-28 four port usb-c
2026-04-29 UPDATE WITH SPO2
2026-05-02 Update for Frameoscope
2026-05-02 Library updates
2026-05-02 Moved to Day 04
2026-05-06 Add USB isolator system spec
